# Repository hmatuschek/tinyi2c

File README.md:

# tiny-i2c -- An augmented i2c-tiny-usb compatible device emulating various I2C devices.

This tiny USB device provides an I2C interface based on the original [i2c-tiny-usb](http://www.harbaum.org/till/i2c_tiny_usb/index.shtml) device. Hence, it is supported by the Linux kernel. Additionally, it is able to emulate various I2C devices in firmware. For example, it is able to emulate the [LM90](http://www.ti.com/product/LM90) temperature sensor by using a simple NTC resistor as a temperature sensor and the build-in temperature sensor of the [ATTiny45](http://www.atmel.com/images/atmel-2586-avr-8-bit-microcontroller-attiny25-attiny45-attiny85_datasheet.pdf).

## License
tinyi2c - Copyright (C) 2016 Hannes Matuschek

This program is free software; you can redistribute it and/or modify it under the terms of the GNU General Public License as published by the Free Software Foundation; either version 2 of the License, or (at your option) any later version.

This program is distributed in the hope that it will be useful, but WITHOUT ANY WARRANTY; without even the implied warranty of MERCHANTABILITY or FITNESS FOR A PARTICULAR PURPOSE. See the GNU General Public License for more details.

You should have received a copy of the GNU General Public License along with this program; if not, write to the Free Software Foundation, Inc., 51 Franklin Street, Fifth Floor, Boston, MA 02110-1301, USA.

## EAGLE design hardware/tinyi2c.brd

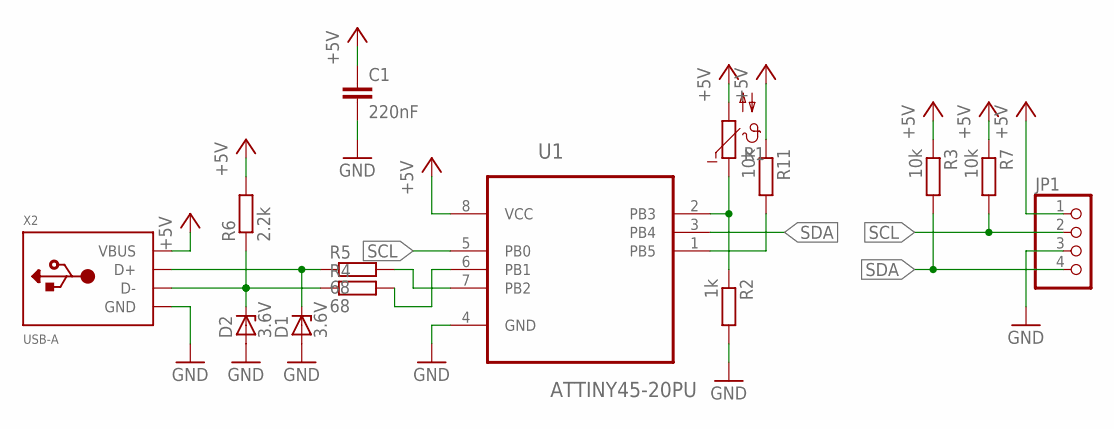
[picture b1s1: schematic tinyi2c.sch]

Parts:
C1: 220nF; C075-032X103
D1: 3.6V; ZDIO-2.5
D2: 3.6V; ZDIO-5
JP1: PINHD-1X4; 1X04
R1: B57164
R2: 1k; 0207/10
R3: 10k; 0207/10
R4, R5: 68; 0204/5
R6: 2.2k; 0204V
R7: 10k; 0204V
R11: 10k; 0204/7
U1: ATTINY45-20PU; DIP254P762X533-8
X2: USB-A; MOLEX_480371000

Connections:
+5V: C1.1, JP1.1, R1.2, R3.1, R6.2, R7.1, R11.1, U1.8 (VCC), X2.1 (VBUS)
GND: C1.2, D1.A, D2.A, JP1.3, R2.2, U1.4 (GND), X2.4 (GND)
unnamed: R1.1, R2.1, U1.2 (PB3)
unnamed: R4.2, U1.6 (PB1)
unnamed: R5.2, U1.7 (PB2)
unnamed: R11.2, U1.1 (PB5)
unnamed: D1.C, R5.1, X2.3 (D+)
unnamed: D2.C, R4.1, R6.1, X2.2 (D-)
SCL: JP1.2, R7.2, U1.5 (PB0)
SDA: JP1.4, R3.2, U1.3 (PB4)

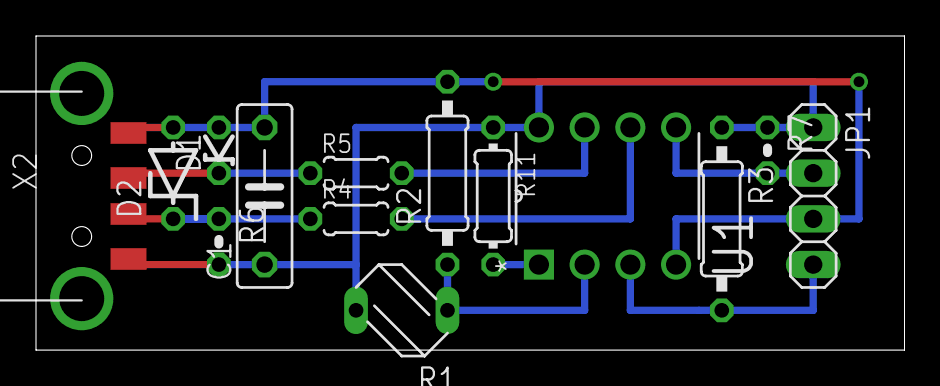
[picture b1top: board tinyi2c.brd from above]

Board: 2 copper layers, 48.2 x 17.5 mm, 14 parts (0 on the bottom side), 10 nets.

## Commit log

2016-08-01 Init.
2016-08-01 Cleanup.
2016-08-09 Fixed.
2016-08-09 Fixed readme.
